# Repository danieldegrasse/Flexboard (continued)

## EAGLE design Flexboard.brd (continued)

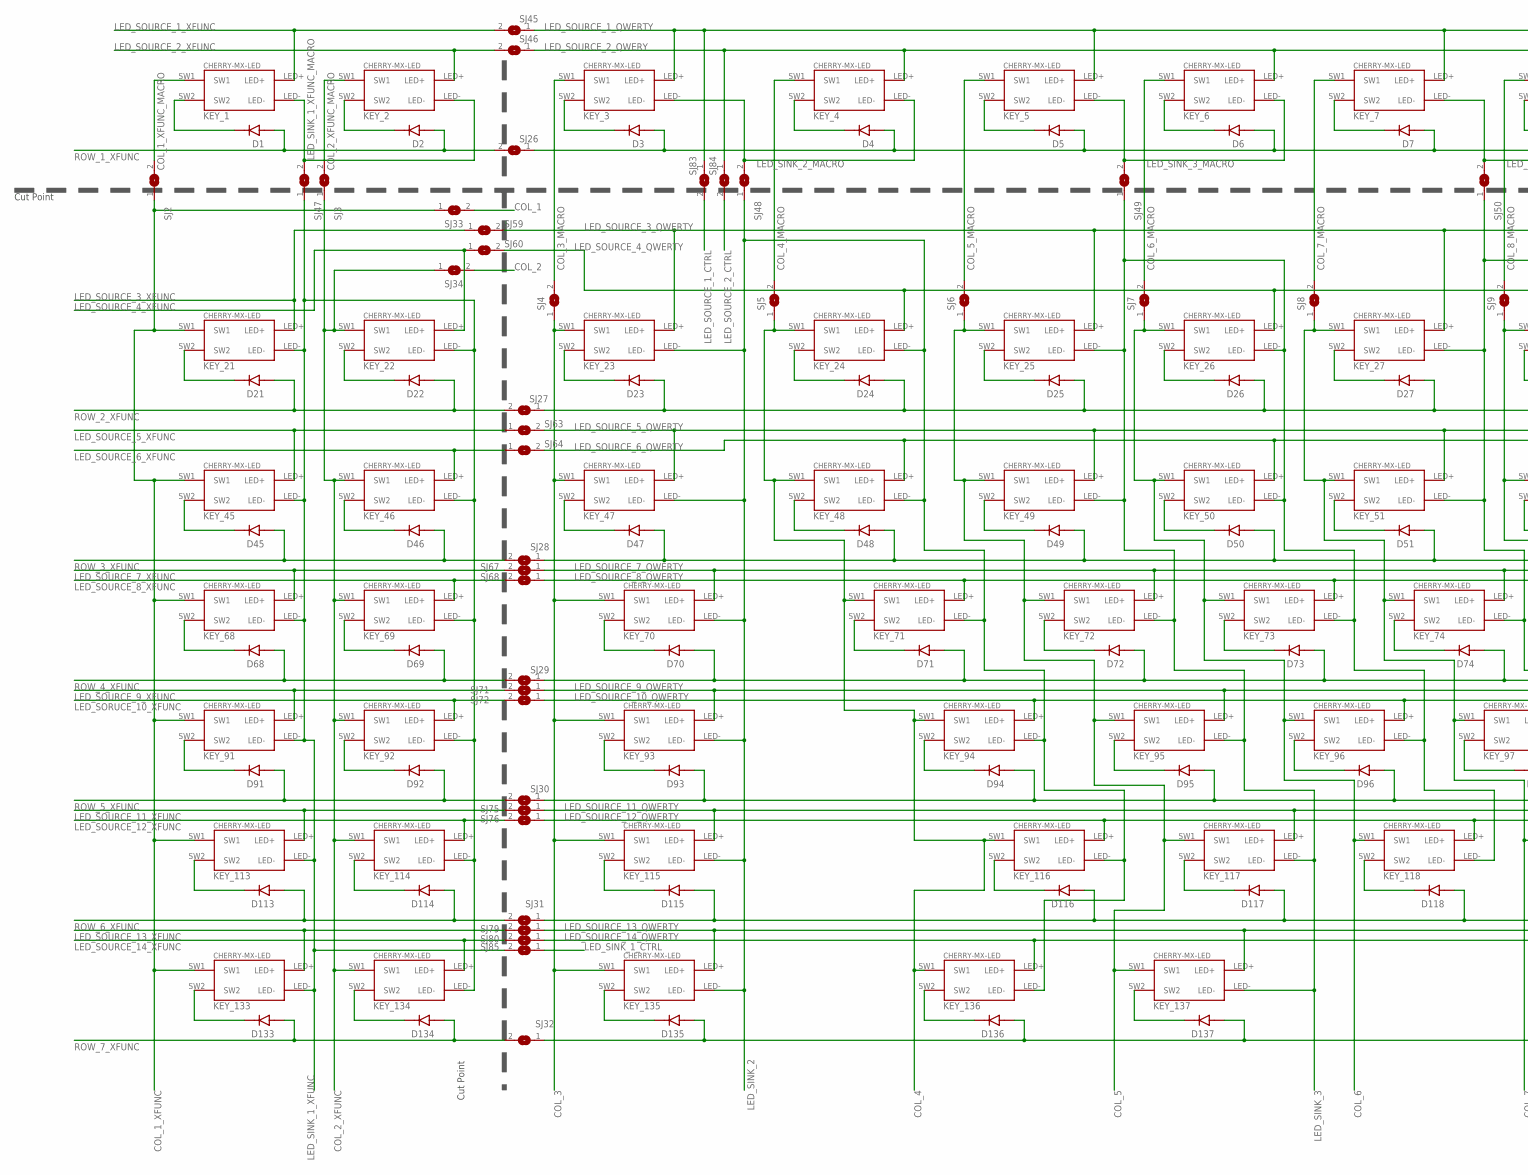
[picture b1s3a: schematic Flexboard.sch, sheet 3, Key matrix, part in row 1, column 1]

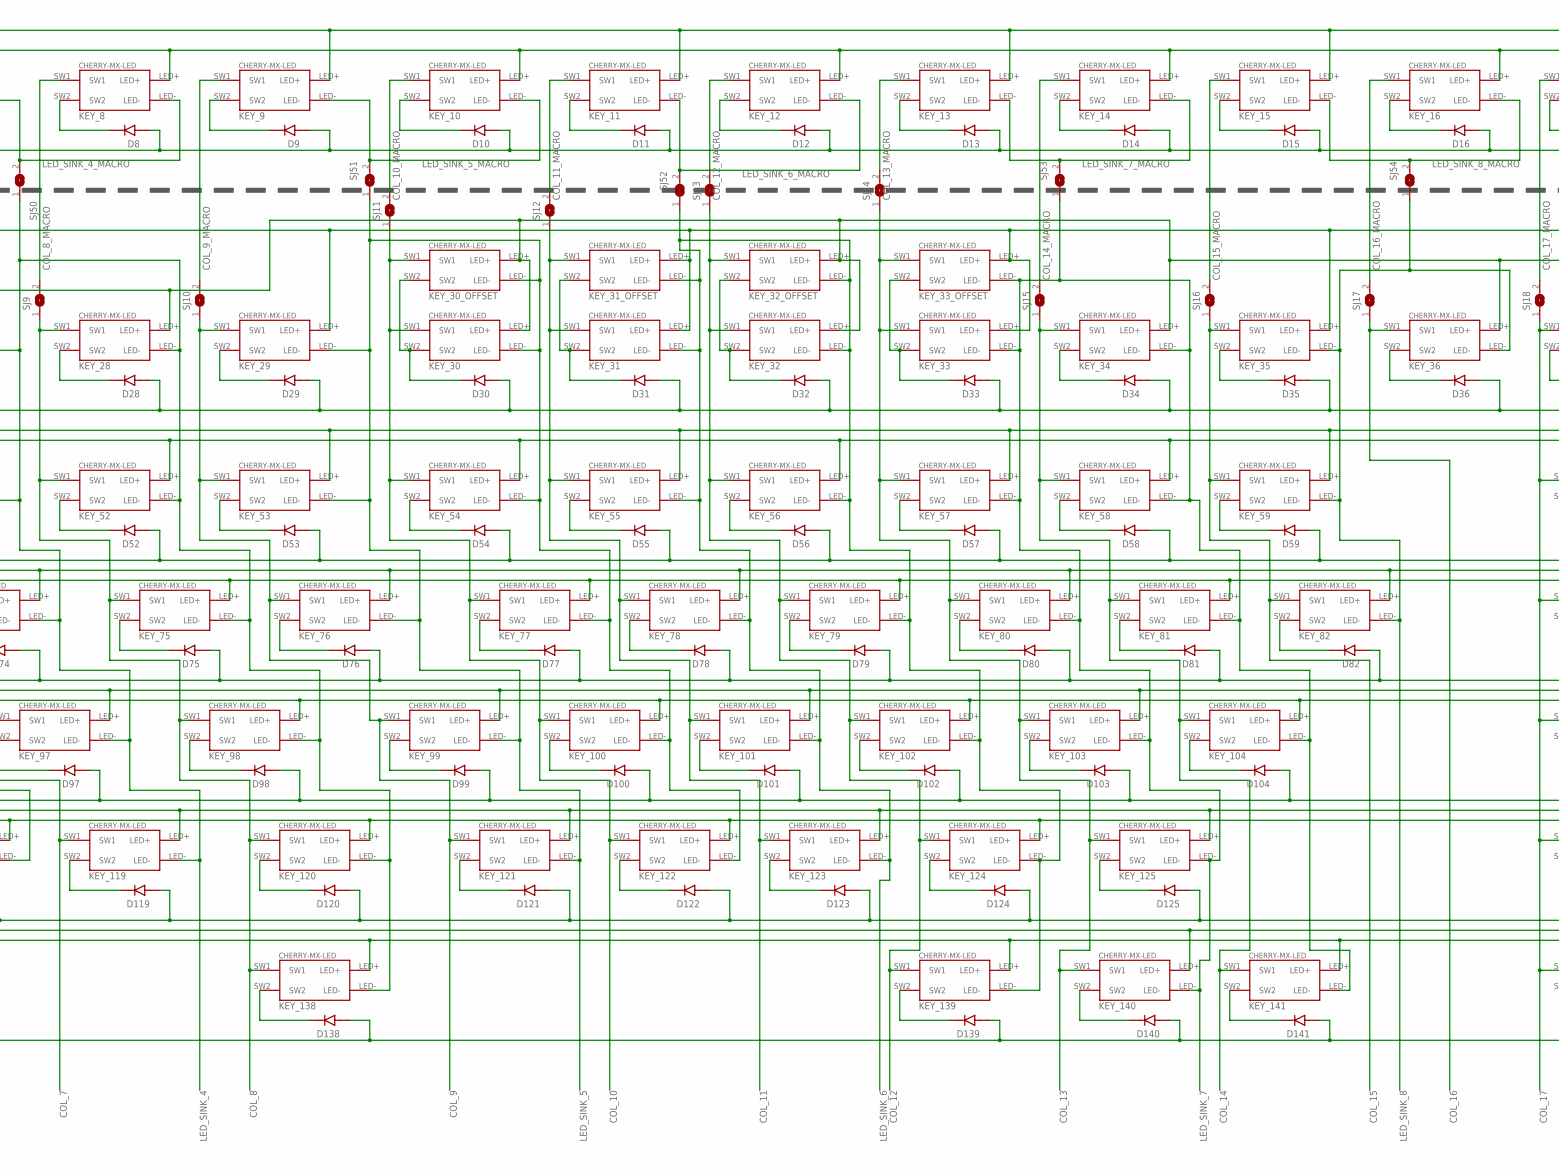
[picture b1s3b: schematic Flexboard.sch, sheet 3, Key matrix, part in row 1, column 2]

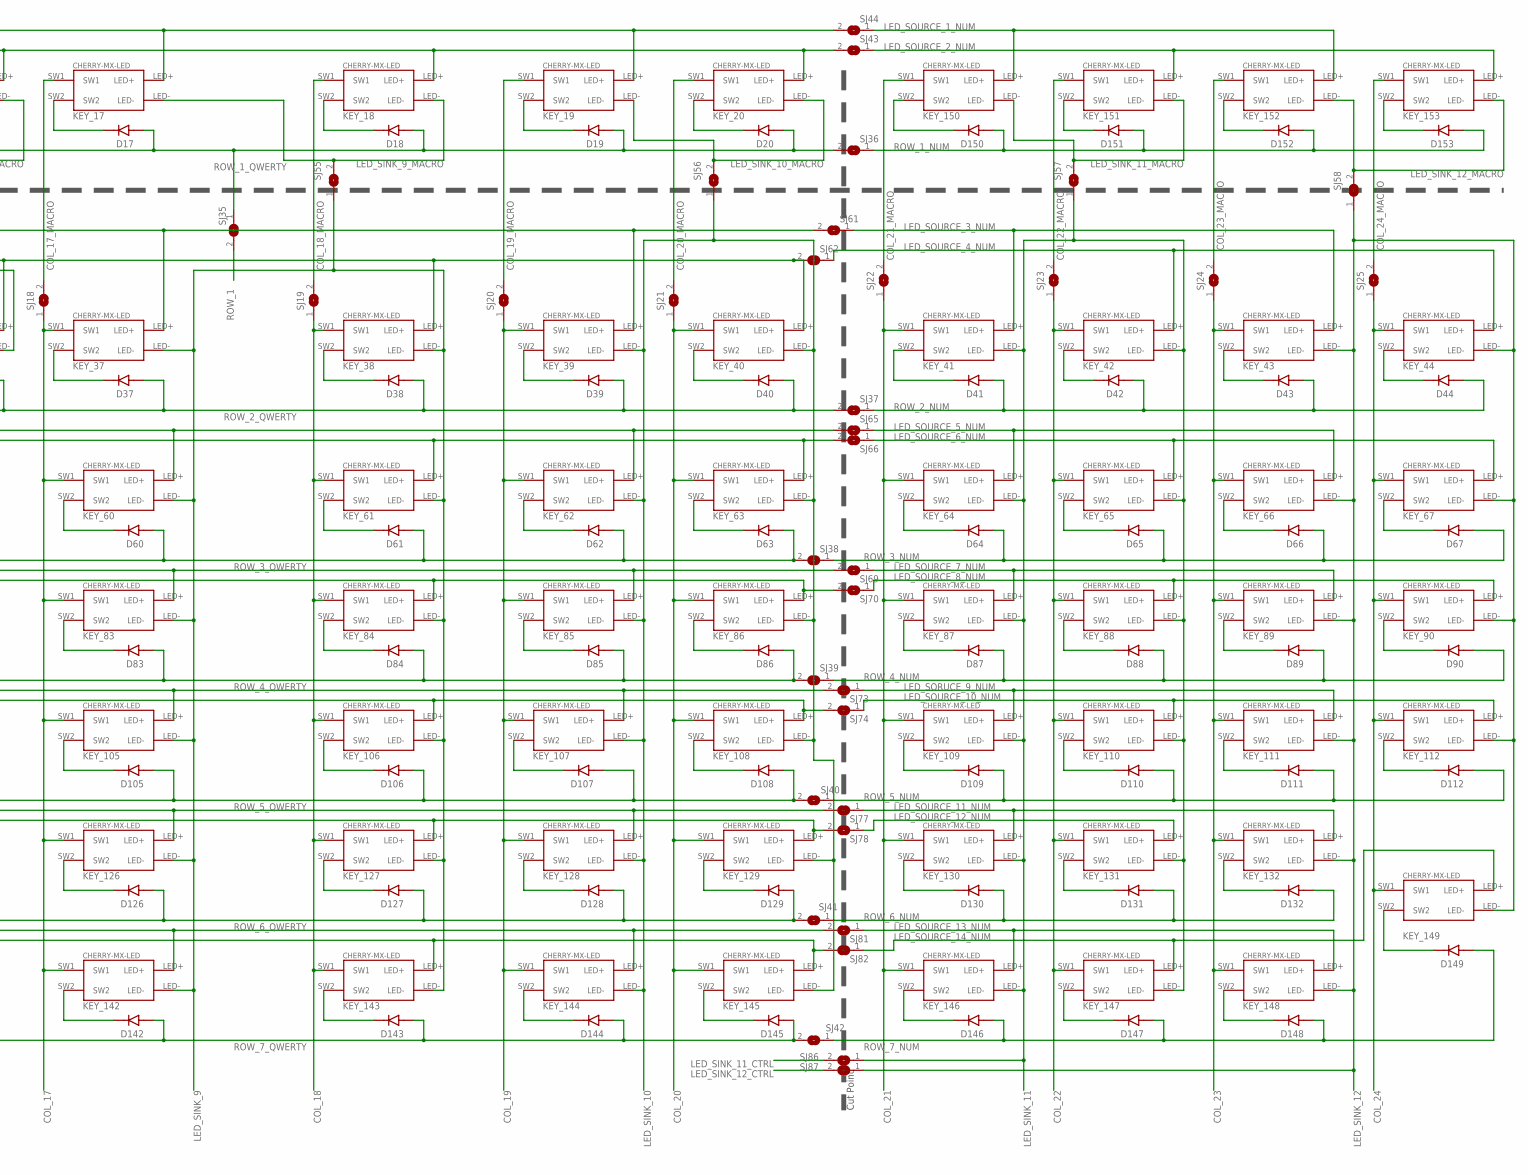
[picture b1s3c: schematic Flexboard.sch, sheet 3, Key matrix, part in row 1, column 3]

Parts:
D1, D2, D3, D4, D5, D6, D7, D8, D9, D10, D11, D12, D13, D14, D15, D16, D17, D18, D19, D20, D21, D22, D23, D24, D25, D26, D27, D28, D29, D30, D31, D32, D33, D34, D35, D36, D37, D38, D39, D40, D41, D42, D43, D44, D45, D46, D47, D48, D49, D50, D51, D52, D53, D54, D55, D56, D57, D58, D59, D60, D61, D62, D63, D64, D65, D66, D67, D68, D69, D70, D71, D72, D73, D74, D75, D76, D77, D78, D79, D80, D81, D82, D83, D84, D85, D86, D87, D88, D89, D90, D91, D92, D93, D94, D95, D96, D97, D98, D99, D100, D101, D102, D103, D104, D105, D106, D107, D108, D109, D110, D111, D112, D113, D114, D115, D116, D117, D118, D119, D120, D121, D122, D123, D124, D125, D126, D127, D128, D129, D130, D131, D132, D133, D134, D135, D136, D137, D138, D139, D140, D141, D142, D143, D144, D145, D146, D147, D148, D149, D150, D151, D152, D153: BAS16LT3G; SOT95P240X111-3N
KEY_1, KEY_2, KEY_3, KEY_4, KEY_5, KEY_6, KEY_7, KEY_8, KEY_9, KEY_10, KEY_11, KEY_12, KEY_13, KEY_14, KEY_15, KEY_16, KEY_17, KEY_18, KEY_19, KEY_20, KEY_21, KEY_22, KEY_23, KEY_24, KEY_25, KEY_26, KEY_27, KEY_28, KEY_29, KEY_30, KEY_31, KEY_32, KEY_33, KEY_34, KEY_35, KEY_36, KEY_37, KEY_38, KEY_39, KEY_40, KEY_41, KEY_42, KEY_43, KEY_44, KEY_45, KEY_46, KEY_47, KEY_48, KEY_49, KEY_50, KEY_51, KEY_52, KEY_53, KEY_54, KEY_55, KEY_56, KEY_57, KEY_58, KEY_59, KEY_60, KEY_61, KEY_62, KEY_63, KEY_64, KEY_65, KEY_66, KEY_67, KEY_68, KEY_69, KEY_70, KEY_71, KEY_72, KEY_73, KEY_74, KEY_75, KEY_76, KEY_77, KEY_78, KEY_79, KEY_80, KEY_81, KEY_82, KEY_83, KEY_84, KEY_85, KEY_86, KEY_87, KEY_88, KEY_89, KEY_90, KEY_91, KEY_92, KEY_93, KEY_94, KEY_95, KEY_96, KEY_97, KEY_98, KEY_99, KEY_100, KEY_101, KEY_102, KEY_103, KEY_104, KEY_105, KEY_106, KEY_107, KEY_108, KEY_109, KEY_110, KEY_111, KEY_112, KEY_113, KEY_114, KEY_115, KEY_116, KEY_117, KEY_118, KEY_119, KEY_120, KEY_121, KEY_122, KEY_123, KEY_124, KEY_125, KEY_126, KEY_127, KEY_128, KEY_129, KEY_130, KEY_131, KEY_132, KEY_133, KEY_134, KEY_135, KEY_136, KEY_137, KEY_138, KEY_139, KEY_140, KEY_141, KEY_142, KEY_143, KEY_144, KEY_145, KEY_146, KEY_147, KEY_148, KEY_149, KEY_150, KEY_151, KEY_152, KEY_153: CHERRY-MX-LED
KEY_30_OFFSET, KEY_31_OFFSET, KEY_32_OFFSET, KEY_33_OFFSET: CHERRY-MX-LED-NOPIN
SJ2, SJ3, SJ4, SJ5, SJ6, SJ7, SJ8, SJ9, SJ10, SJ11, SJ12, SJ13, SJ14, SJ15, SJ16, SJ17, SJ18, SJ19, SJ20, SJ21, SJ22, SJ23, SJ24, SJ25, SJ26, SJ27, SJ28, SJ29, SJ30, SJ31, SJ32, SJ33, SJ34, SJ35, SJ36, SJ37, SJ38, SJ39, SJ40, SJ41, SJ42, SJ43, SJ44, SJ45, SJ46, SJ47, SJ48, SJ49, SJ50, SJ51, SJ52, SJ53, SJ54, SJ55, SJ56, SJ57, SJ58, SJ59, SJ60, SJ61, SJ62, SJ63, SJ64, SJ65, SJ66, SJ67, SJ68, SJ69, SJ70, SJ71, SJ72, SJ73, SJ74, SJ75, SJ76, SJ77, SJ78, SJ79, SJ80, SJ81, SJ82, SJ83, SJ84, SJ85, SJ86, SJ87: SJW

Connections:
COL_1: SJ33.2; also elsewhere on the board
COL_1_XFUNC: KEY_21.SW1, KEY_45.SW1, KEY_68.SW1, KEY_91.SW1, KEY_113.SW1, KEY_133.SW1, SJ2.1, SJ33.1
COL_1_XFUNC_MACRO: KEY_1.SW1, SJ2.2
COL_2: SJ34.2; also elsewhere on the board
COL_2_XFUNC: KEY_22.SW1, KEY_46.SW1, KEY_69.SW1, KEY_92.SW1, KEY_114.SW1, KEY_134.SW1, SJ3.1, SJ34.1
COL_2_XFUNC_MACRO: KEY_2.SW1, SJ3.2
COL_3: KEY_23.SW1, KEY_47.SW1, KEY_70.SW1, KEY_93.SW1, KEY_115.SW1, KEY_135.SW1, SJ4.1; also elsewhere on the board
COL_3_MACRO: KEY_3.SW1, SJ4.2
COL_4: KEY_24.SW1, KEY_48.SW1, KEY_71.SW1, KEY_94.SW1, KEY_116.SW1, KEY_136.SW1, SJ5.1; also elsewhere on the board
COL_4_MACRO: KEY_4.SW1, SJ5.2
COL_5: KEY_25.SW1, KEY_49.SW1, KEY_72.SW1, KEY_95.SW1, KEY_117.SW1, KEY_137.SW1, SJ6.1; also elsewhere on the board
COL_5_MACRO: KEY_5.SW1, SJ6.2
COL_6: KEY_26.SW1, KEY_50.SW1, KEY_73.SW1, KEY_96.SW1, KEY_118.SW1, SJ7.1; also elsewhere on the board
COL_6_MACRO: KEY_6.SW1, SJ7.2
COL_7: KEY_27.SW1, KEY_51.SW1, KEY_74.SW1, KEY_97.SW1, KEY_119.SW1, SJ8.1; also elsewhere on the board
COL_7_MACRO: KEY_7.SW1, SJ8.2
COL_8: KEY_28.SW1, KEY_52.SW1, KEY_75.SW1, KEY_98.SW1, KEY_120.SW1, KEY_138.SW1, SJ9.1; also elsewhere on the board
COL_8_MACRO: KEY_8.SW1, SJ9.2
COL_9: KEY_29.SW1, KEY_53.SW1, KEY_76.SW1, KEY_99.SW1, KEY_121.SW1, SJ10.1; also elsewhere on the board
COL_9_MACRO: KEY_9.SW1, SJ10.2
COL_10: KEY_30.SW1, KEY_30_OFFSET.SW1, KEY_54.SW1, KEY_77.SW1, KEY_100.SW1, KEY_122.SW1, SJ11.1; also elsewhere on the board
COL_10_MACRO: KEY_10.SW1, SJ11.2
COL_11: KEY_31.SW1, KEY_31_OFFSET.SW1, KEY_55.SW1, KEY_78.SW1, KEY_101.SW1, KEY_123.SW1, SJ12.1; also elsewhere on the board
COL_11_MACRO: KEY_11.SW1, SJ12.2
COL_12: KEY_32.SW1, KEY_32_OFFSET.SW1, KEY_56.SW1, KEY_79.SW1, KEY_102.SW1, KEY_124.SW1, KEY_139.SW1, SJ13.1; also elsewhere on the board
COL_12_MACRO: KEY_12.SW1, SJ13.2
COL_13: KEY_33.SW1, KEY_33_OFFSET.SW1, KEY_57.SW1, KEY_80.SW1, KEY_103.SW1, KEY_125.SW1, KEY_140.SW1, SJ14.1; also elsewhere on the board
COL_13_MACRO: KEY_13.SW1, SJ14.2
COL_14: KEY_34.SW1, KEY_58.SW1, KEY_81.SW1, KEY_104.SW1, KEY_141.SW1, SJ15.1; also elsewhere on the board
COL_14_MACRO: KEY_14.SW1, SJ15.2
COL_15: KEY_35.SW1, KEY_59.SW1, KEY_82.SW1, SJ16.1; also elsewhere on the board
COL_15_MACRO: KEY_15.SW1, SJ16.2
COL_16: KEY_36.SW1, SJ17.1; also elsewhere on the board
COL_16_MACRO: KEY_16.SW1, SJ17.2
COL_17: KEY_37.SW1, KEY_60.SW1, KEY_83.SW1, KEY_105.SW1, KEY_126.SW1, KEY_142.SW1, SJ18.1; also elsewhere on the board
COL_17_MACRO: KEY_17.SW1, SJ18.2
COL_18: KEY_38.SW1, KEY_61.SW1, KEY_84.SW1, KEY_106.SW1, KEY_127.SW1, KEY_143.SW1, SJ19.1; also elsewhere on the board
COL_18_MACRO: KEY_18.SW1, SJ19.2
COL_19: KEY_39.SW1, KEY_62.SW1, KEY_85.SW1, KEY_107.SW1, KEY_128.SW1, KEY_144.SW1, SJ20.1; also elsewhere on the board
COL_19_MACRO: KEY_19.SW1, SJ20.2
COL_20: KEY_40.SW1, KEY_63.SW1, KEY_86.SW1, KEY_108.SW1, KEY_129.SW1, KEY_145.SW1, SJ21.1; also elsewhere on the board
COL_20_MACRO: KEY_20.SW1, SJ21.2
COL_21: KEY_41.SW1, KEY_64.SW1, KEY_87.SW1, KEY_109.SW1, KEY_130.SW1, KEY_146.SW1, SJ22.1; also elsewhere on the board
COL_21_MACRO: KEY_150.SW1, SJ22.2
COL_22: KEY_42.SW1, KEY_65.SW1, KEY_88.SW1, KEY_110.SW1, KEY_131.SW1, KEY_147.SW1, SJ23.1; also elsewhere on the board
COL_22_MACRO: KEY_151.SW1, SJ23.2
COL_23: KEY_43.SW1, KEY_66.SW1, KEY_89.SW1, KEY_111.SW1, KEY_132.SW1, KEY_148.SW1, SJ24.1; also elsewhere on the board
COL_23_MACRO: KEY_152.SW1, SJ24.2
COL_24: KEY_44.SW1, KEY_67.SW1, KEY_90.SW1, KEY_112.SW1, KEY_149.SW1, SJ25.1; also elsewhere on the board
COL_24_MACRO: KEY_153.SW1, SJ25.2
LED_SINK_1_CTRL: SJ85.1; also elsewhere on the board
LED_SINK_1_XFUNC: KEY_21.LED-, KEY_22.LED-, KEY_45.LED-, KEY_46.LED-, KEY_68.LED-, KEY_69.LED-, KEY_91.LED-, KEY_92.LED-, KEY_113.LED-, KEY_114.LED-, KEY_133.LED-, KEY_134.LED-, SJ47.1, SJ85.2
LED_SINK_1_XFUNC_MACRO: KEY_1.LED-, KEY_2.LED-, SJ47.2
LED_SINK_2: KEY_23.LED-, KEY_24.LED-, KEY_47.LED-, KEY_48.LED-, KEY_70.LED-, KEY_71.LED-, KEY_93.LED-, KEY_94.LED-, KEY_115.LED-, KEY_116.LED-, KEY_135.LED-, KEY_136.LED-, SJ48.1; also elsewhere on the board
LED_SINK_2_MACRO: KEY_3.LED-, KEY_4.LED-, SJ48.2
LED_SINK_3: KEY_25.LED-, KEY_26.LED-, KEY_49.LED-, KEY_50.LED-, KEY_72.LED-, KEY_73.LED-, KEY_95.LED-, KEY_96.LED-, KEY_117.LED-, KEY_118.LED-, KEY_137.LED-, SJ49.1; also elsewhere on the board
LED_SINK_3_MACRO: KEY_5.LED-, KEY_6.LED-, SJ49.2
LED_SINK_4: KEY_27.LED-, KEY_28.LED-, KEY_51.LED-, KEY_52.LED-, KEY_74.LED-, KEY_75.LED-, KEY_97.LED-, KEY_98.LED-, KEY_119.LED-, KEY_120.LED-, KEY_138.LED-, SJ50.1; also elsewhere on the board
LED_SINK_4_MACRO: KEY_7.LED-, KEY_8.LED-, SJ50.2
LED_SINK_5: KEY_29.LED-, KEY_30.LED-, KEY_30_OFFSET.LED-, KEY_53.LED-, KEY_54.LED-, KEY_76.LED-, KEY_77.LED-, KEY_99.LED-, KEY_100.LED-, KEY_121.LED-, KEY_122.LED-, SJ51.1; also elsewhere on the board
LED_SINK_5_MACRO: KEY_9.LED-, KEY_10.LED-, SJ51.2
LED_SINK_6: KEY_31.LED-, KEY_31_OFFSET.LED-, KEY_32.LED-, KEY_32_OFFSET.LED-, KEY_55.LED-, KEY_56.LED-, KEY_78.LED-, KEY_79.LED-, KEY_101.LED-, KEY_102.LED-, KEY_123.LED-, KEY_124.LED-, KEY_139.LED-, SJ52.1; also elsewhere on the board
LED_SINK_6_MACRO: KEY_11.LED-, KEY_12.LED-, SJ52.2
LED_SINK_7: KEY_33.LED-, KEY_33_OFFSET.LED-, KEY_34.LED-, KEY_57.LED-, KEY_58.LED-, KEY_80.LED-, KEY_81.LED-, KEY_103.LED-, KEY_104.LED-, KEY_125.LED-, KEY_140.LED-, KEY_141.LED-, SJ53.1; also elsewhere on the board
LED_SINK_7_MACRO: KEY_13.LED-, KEY_14.LED-, SJ53.2
LED_SINK_8: KEY_35.LED-, KEY_36.LED-, KEY_59.LED-, KEY_82.LED-, SJ54.1; also elsewhere on the board
LED_SINK_8_MACRO: KEY_15.LED-, KEY_16.LED-, SJ54.2
LED_SINK_9: KEY_37.LED-, KEY_38.LED-, KEY_60.LED-, KEY_61.LED-, KEY_83.LED-, KEY_84.LED-, KEY_105.LED-, KEY_106.LED-, KEY_126.LED-, KEY_127.LED-, KEY_142.LED-, KEY_143.LED-, SJ55.1; also elsewhere on the board
LED_SINK_9_MACRO: KEY_17.LED-, KEY_18.LED-, SJ55.2
LED_SINK_10: KEY_39.LED-, KEY_40.LED-, KEY_62.LED-, KEY_63.LED-, KEY_85.LED-, KEY_86.LED-, KEY_107.LED-, KEY_108.LED-, KEY_128.LED-, KEY_129.LED-, KEY_144.LED-, KEY_145.LED-, SJ56.1; also elsewhere on the board
LED_SINK_10_MACRO: KEY_19.LED-, KEY_20.LED-, SJ56.2
LED_SINK_11: KEY_41.LED-, KEY_42.LED-, KEY_64.LED-, KEY_65.LED-, KEY_87.LED-, KEY_88.LED-, KEY_109.LED-, KEY_110.LED-, KEY_130.LED-, KEY_131.LED-, KEY_146.LED-, KEY_147.LED-, SJ57.1, SJ86.1
LED_SINK_11_CTRL: SJ86.2; also elsewhere on the board
LED_SINK_11_MACRO: KEY_150.LED-, KEY_151.LED-, SJ57.2
LED_SINK_12: KEY_43.LED-, KEY_44.LED-, KEY_66.LED-, KEY_67.LED-, KEY_89.LED-, KEY_90.LED-, KEY_111.LED-, KEY_112.LED-, KEY_132.LED-, KEY_148.LED-, KEY_149.LED-, SJ58.1, SJ87.1
LED_SINK_12_CTRL: SJ87.2; also elsewhere on the board
LED_SINK_12_MACRO: KEY_152.LED-, KEY_153.LED-, SJ58.2
LED_SORUCE_9_NUM: KEY_109.LED+, KEY_111.LED+, SJ73.1
LED_SORUCE_10_XFUNC: KEY_92.LED+, SJ72.2
LED_SOURCE_1_CTRL: SJ83.2; also elsewhere on the board
LED_SOURCE_1_NUM: KEY_150.LED+, KEY_152.LED+, SJ44.1
LED_SOURCE_1_QWERTY: KEY_3.LED+, KEY_5.LED+, KEY_7.LED+, KEY_9.LED+, KEY_11.LED+, KEY_13.LED+, KEY_15.LED+, KEY_17.LED+, KEY_19.LED+, SJ44.2, SJ45.1, SJ83.1
LED_SOURCE_1_XFUNC: KEY_1.LED+, SJ45.2
LED_SOURCE_2_CTRL: SJ84.2; also elsewhere on the board
LED_SOURCE_2_NUM: KEY_151.LED+, KEY_153.LED+, SJ43.1
LED_SOURCE_2_QWERY: KEY_4.LED+, KEY_6.LED+, KEY_8.LED+, KEY_10.LED+, KEY_12.LED+, KEY_14.LED+, KEY_16.LED+, KEY_18.LED+, KEY_20.LED+, SJ43.2, SJ46.1, SJ84.1
LED_SOURCE_2_XFUNC: KEY_2.LED+, SJ46.2
LED_SOURCE_3_NUM: KEY_41.LED+, KEY_43.LED+, SJ61.1
LED_SOURCE_3_QWERTY: KEY_23.LED+, KEY_25.LED+, KEY_27.LED+, KEY_29.LED+, KEY_31.LED+, KEY_31_OFFSET.LED+, KEY_33.LED+, KEY_33_OFFSET.LED+, KEY_35.LED+, KEY_37.LED+, KEY_39.LED+, SJ59.2, SJ61.2; also elsewhere on the board
LED_SOURCE_3_XFUNC: KEY_21.LED+, SJ59.1
LED_SOURCE_4_NUM: KEY_42.LED+, KEY_44.LED+, SJ62.1
LED_SOURCE_4_QWERTY: KEY_24.LED+, KEY_26.LED+, KEY_28.LED+, KEY_30.LED+, KEY_30_OFFSET.LED+, KEY_32.LED+, KEY_32_OFFSET.LED+, KEY_34.LED+, KEY_36.LED+, KEY_38.LED+, KEY_40.LED+, SJ60.2, SJ62.2; also elsewhere on the board
LED_SOURCE_4_XFUNC: KEY_22.LED+, SJ60.1
LED_SOURCE_5_NUM: KEY_64.LED+, KEY_66.LED+, SJ65.1
LED_SOURCE_5_QWERTY: KEY_47.LED+, KEY_49.LED+, KEY_51.LED+, KEY_53.LED+, KEY_55.LED+, KEY_57.LED+, KEY_59.LED+, KEY_60.LED+, KEY_62.LED+, SJ63.2, SJ65.2; also elsewhere on the board
LED_SOURCE_5_XFUNC: KEY_45.LED+, SJ63.1
LED_SOURCE_6_NUM: KEY_65.LED+, KEY_67.LED+, SJ66.1
LED_SOURCE_6_QWERTY: KEY_48.LED+, KEY_50.LED+, KEY_52.LED+, KEY_54.LED+, KEY_56.LED+, KEY_58.LED+, KEY_61.LED+, KEY_63.LED+, SJ64.2, SJ66.2; also elsewhere on the board
LED_SOURCE_6_XFUNC: KEY_46.LED+, SJ64.1
LED_SOURCE_7_NUM: KEY_87.LED+, KEY_89.LED+, SJ69.1
LED_SOURCE_7_QWERTY: KEY_70.LED+, KEY_72.LED+, KEY_74.LED+, KEY_76.LED+, KEY_78.LED+, KEY_80.LED+, KEY_82.LED+, KEY_83.LED+, KEY_85.LED+, SJ67.1, SJ69.2; also elsewhere on the board
LED_SOURCE_7_XFUNC: KEY_68.LED+, SJ67.2
LED_SOURCE_8_NUM: KEY_88.LED+, KEY_90.LED+, SJ70.1
LED_SOURCE_8_QWERTY: KEY_71.LED+, KEY_73.LED+, KEY_75.LED+, KEY_77.LED+, KEY_79.LED+, KEY_81.LED+, KEY_84.LED+, KEY_86.LED+, SJ68.1, SJ70.2; also elsewhere on the board
LED_SOURCE_8_XFUNC: KEY_69.LED+, SJ68.2
LED_SOURCE_9_QWERTY: KEY_93.LED+, KEY_95.LED+, KEY_97.LED+, KEY_99.LED+, KEY_101.LED+, KEY_103.LED+, KEY_105.LED+, KEY_107.LED+, SJ71.1, SJ73.2; also elsewhere on the board
LED_SOURCE_9_XFUNC: KEY_91.LED+, SJ71.2
LED_SOURCE_10_NUM: KEY_110.LED+, KEY_112.LED+, SJ74.1
LED_SOURCE_10_QWERTY: KEY_94.LED+, KEY_96.LED+, KEY_98.LED+, KEY_100.LED+, KEY_102.LED+, KEY_104.LED+, KEY_106.LED+, KEY_108.LED+, SJ72.1, SJ74.2; also elsewhere on the board
LED_SOURCE_11_NUM: KEY_130.LED+, KEY_132.LED+, SJ77.1
LED_SOURCE_11_QWERTY: KEY_115.LED+, KEY_117.LED+, KEY_119.LED+, KEY_121.LED+, KEY_123.LED+, KEY_125.LED+, KEY_126.LED+, KEY_128.LED+, SJ75.1, SJ77.2; also elsewhere on the board
LED_SOURCE_11_XFUNC: KEY_113.LED+, SJ75.2
LED_SOURCE_12_NUM: KEY_131.LED+, SJ78.1
LED_SOURCE_12_QWERTY: KEY_116.LED+, KEY_118.LED+, KEY_120.LED+, KEY_122.LED+, KEY_124.LED+, KEY_127.LED+, KEY_129.LED+, SJ76.1, SJ78.2; also elsewhere on the board
LED_SOURCE_12_XFUNC: KEY_114.LED+, SJ76.2
LED_SOURCE_13_NUM: KEY_146.LED+, KEY_148.LED+, SJ81.1
LED_SOURCE_13_QWERTY: KEY_135.LED+, KEY_137.LED+, KEY_140.LED+, KEY_142.LED+, KEY_144.LED+, SJ79.1, SJ81.2; also elsewhere on the board
LED_SOURCE_13_XFUNC: KEY_133.LED+, SJ79.2
LED_SOURCE_14_NUM: KEY_147.LED+, KEY_149.LED+, SJ82.1
LED_SOURCE_14_QWERTY: KEY_136.LED+, KEY_138.LED+, KEY_139.LED+, KEY_141.LED+, KEY_143.LED+, KEY_145.LED+, SJ80.1, SJ82.2; also elsewhere on the board
LED_SOURCE_14_XFUNC: KEY_134.LED+, SJ80.2
unnamed: D1.3 (C), KEY_1.SW2
unnamed: D2.3 (C), KEY_2.SW2
unnamed: D3.3 (C), KEY_3.SW2
unnamed: D4.3 (C), KEY_4.SW2
unnamed: D5.3 (C), KEY_5.SW2
unnamed: D6.3 (C), KEY_6.SW2
unnamed: D7.3 (C), KEY_7.SW2
unnamed: D8.3 (C), KEY_8.SW2
unnamed: D9.3 (C), KEY_9.SW2
unnamed: D10.3 (C), KEY_10.SW2
unnamed: D31.3 (C), KEY_31.SW2, KEY_31_OFFSET.SW2
unnamed: D11.3 (C), KEY_11.SW2
unnamed: D40.3 (C), KEY_40.SW2
unnamed: D12.3 (C), KEY_12.SW2
unnamed: D39.3 (C), KEY_39.SW2
unnamed: D13.3 (C), KEY_13.SW2
unnamed: D25.3 (C), KEY_25.SW2
unnamed: D14.3 (C), KEY_14.SW2
unnamed: D38.3 (C), KEY_38.SW2
unnamed: D15.3 (C), KEY_15.SW2
unnamed: D35.3 (C), KEY_35.SW2
unnamed: D16.3 (C), KEY_16.SW2
unnamed: D34.3 (C), KEY_34.SW2
unnamed: D17.3 (C), KEY_17.SW2
unnamed: D37.3 (C), KEY_37.SW2
unnamed: D18.3 (C), KEY_18.SW2
unnamed: D30.3 (C), KEY_30.SW2, KEY_30_OFFSET.SW2
unnamed: D19.3 (C), KEY_19.SW2
unnamed: D36.3 (C), KEY_36.SW2
unnamed: D20.3 (C), KEY_20.SW2
unnamed: D33.3 (C), KEY_33.SW2, KEY_33_OFFSET.SW2
unnamed: D23.3 (C), KEY_23.SW2
unnamed: D32.3 (C), KEY_32.SW2, KEY_32_OFFSET.SW2
unnamed: D29.3 (C), KEY_29.SW2
unnamed: D24.3 (C), KEY_24.SW2
unnamed: D28.3 (C), KEY_28.SW2
unnamed: D27.3 (C), KEY_27.SW2
unnamed: D22.3 (C), KEY_22.SW2
unnamed: D26.3 (C), KEY_26.SW2
unnamed: D21.3 (C), KEY_21.SW2
unnamed: D45.3 (C), KEY_45.SW2
unnamed: D41.3 (C), KEY_41.SW2
unnamed: D46.3 (C), KEY_46.SW2
unnamed: D67.3 (C), KEY_67.SW2
unnamed: D66.3 (C), KEY_66.SW2
unnamed: D68.3 (C), KEY_68.SW2
unnamed: D65.3 (C), KEY_65.SW2
unnamed: D64.3 (C), KEY_64.SW2
unnamed: D63.3 (C), KEY_63.SW2
unnamed: D62.3 (C), KEY_62.SW2
unnamed: D61.3 (C), KEY_61.SW2
unnamed: D52.3 (C), KEY_52.SW2
unnamed: D49.3 (C), KEY_49.SW2
unnamed: D60.3 (C), KEY_60.SW2
unnamed: D51.3 (C), KEY_51.SW2
unnamed: D59.3 (C), KEY_59.SW2
unnamed: D58.3 (C), KEY_58.SW2
unnamed: D57.3 (C), KEY_57.SW2
unnamed: D50.3 (C), KEY_50.SW2
unnamed: D48.3 (C), KEY_48.SW2
unnamed: D56.3 (C), KEY_56.SW2
unnamed: D69.3 (C), KEY_69.SW2
unnamed: D55.3 (C), KEY_55.SW2
unnamed: D47.3 (C), KEY_47.SW2
unnamed: D54.3 (C), KEY_54.SW2
unnamed: D90.3 (C), KEY_90.SW2
unnamed: D53.3 (C), KEY_53.SW2
unnamed: D150.3 (C), KEY_150.SW2
unnamed: D89.3 (C), KEY_89.SW2
unnamed: D87.3 (C), KEY_87.SW2
unnamed: D70.3 (C), KEY_70.SW2
unnamed: D88.3 (C), KEY_88.SW2
unnamed: D83.3 (C), KEY_83.SW2
unnamed: D86.3 (C), KEY_86.SW2
unnamed: D71.3 (C), KEY_71.SW2
unnamed: D151.3 (C), KEY_151.SW2
unnamed: D72.3 (C), KEY_72.SW2
unnamed: D84.3 (C), KEY_84.SW2
unnamed: D73.3 (C), KEY_73.SW2
unnamed: D74.3 (C), KEY_74.SW2
unnamed: D85.3 (C), KEY_85.SW2
unnamed: D75.3 (C), KEY_75.SW2
unnamed: D112.3 (C), KEY_112.SW2
unnamed: D76.3 (C), KEY_76.SW2
unnamed: D111.3 (C), KEY_111.SW2
unnamed: D77.3 (C), KEY_77.SW2
unnamed: D110.3 (C), KEY_110.SW2
unnamed: D78.3 (C), KEY_78.SW2
unnamed: D96.3 (C), KEY_96.SW2
unnamed: D79.3 (C), KEY_79.SW2
unnamed: D109.3 (C), KEY_109.SW2
unnamed: D80.3 (C), KEY_80.SW2
unnamed: D113.3 (C), KEY_113.SW2
unnamed: D81.3 (C), KEY_81.SW2
unnamed: D108.3 (C), KEY_108.SW2
unnamed: D82.3 (C), KEY_82.SW2
unnamed: D100.3 (C), KEY_100.SW2
unnamed: D107.3 (C), KEY_107.SW2
unnamed: D106.3 (C), KEY_106.SW2
unnamed: D152.3 (C), KEY_152.SW2
unnamed: D99.3 (C), KEY_99.SW2
unnamed: D105.3 (C), KEY_105.SW2
unnamed: D104.3 (C), KEY_104.SW2
unnamed: D95.3 (C), KEY_95.SW2
unnamed: D103.3 (C), KEY_103.SW2
unnamed: D98.3 (C), KEY_98.SW2
unnamed: D97.3 (C), KEY_97.SW2
unnamed: D102.3 (C), KEY_102.SW2
unnamed: D101.3 (C), KEY_101.SW2
unnamed: D114.3 (C), KEY_114.SW2
unnamed: D94.3 (C), KEY_94.SW2
unnamed: D132.3 (C), KEY_132.SW2
unnamed: D93.3 (C), KEY_93.SW2
unnamed: D153.3 (C), KEY_153.SW2
unnamed: D92.3 (C), KEY_92.SW2
unnamed: D91.3 (C), KEY_91.SW2
unnamed: D131.3 (C), KEY_131.SW2
unnamed: D129.3 (C), KEY_129.SW2
unnamed: D130.3 (C), KEY_130.SW2
unnamed: D128.3 (C), KEY_128.SW2
unnamed: D124.3 (C), KEY_124.SW2
unnamed: D127.3 (C), KEY_127.SW2
unnamed: D125.3 (C), KEY_125.SW2
unnamed: D126.3 (C), KEY_126.SW2
unnamed: D133.3 (C), KEY_133.SW2
unnamed: D123.3 (C), KEY_123.SW2
unnamed: D122.3 (C), KEY_122.SW2
unnamed: D134.3 (C), KEY_134.SW2
unnamed: D121.3 (C), KEY_121.SW2
unnamed: D149.3 (C), KEY_149.SW2
unnamed: D120.3 (C), KEY_120.SW2
unnamed: D42.3 (C), KEY_42.SW2
unnamed: D119.3 (C), KEY_119.SW2
unnamed: D146.3 (C), KEY_146.SW2
unnamed: D118.3 (C), KEY_118.SW2
unnamed: D148.3 (C), KEY_148.SW2
unnamed: D117.3 (C), KEY_117.SW2
unnamed: D144.3 (C), KEY_144.SW2
unnamed: D116.3 (C), KEY_116.SW2
unnamed: D147.3 (C), KEY_147.SW2
unnamed: D145.3 (C), KEY_145.SW2
unnamed: D115.3 (C), KEY_115.SW2
unnamed: D143.3 (C), KEY_143.SW2
unnamed: D135.3 (C), KEY_135.SW2
unnamed: D142.3 (C), KEY_142.SW2
unnamed: D141.3 (C), KEY_141.SW2
unnamed: D140.3 (C), KEY_140.SW2
unnamed: D139.3 (C), KEY_139.SW2
unnamed: D43.3 (C), KEY_43.SW2
unnamed: D138.3 (C), KEY_138.SW2
unnamed: D137.3 (C), KEY_137.SW2
unnamed: D136.3 (C), KEY_136.SW2
unnamed: D44.3 (C), KEY_44.SW2
ROW_1: SJ35.2; also elsewhere on the board
ROW_1_NUM: D150.1 (A), D151.1 (A), D152.1 (A), D153.1 (A), SJ36.1
ROW_1_QWERTY: D3.1 (A), D4.1 (A), D5.1 (A), D6.1 (A), D7.1 (A), D8.1 (A), D9.1 (A), D10.1 (A), D11.1 (A), D12.1 (A), D13.1 (A), D14.1 (A), D15.1 (A), D16.1 (A), D17.1 (A), D18.1 (A), D19.1 (A), D20.1 (A), SJ26.1, SJ35.1, SJ36.2
ROW_1_XFUNC: D1.1 (A), D2.1 (A), SJ26.2
ROW_2_NUM: D41.1 (A), D42.1 (A), D43.1 (A), D44.1 (A), SJ37.1
ROW_2_QWERTY: D23.1 (A), D24.1 (A), D25.1 (A), D26.1 (A), D27.1 (A), D28.1 (A), D29.1 (A), D30.1 (A), D31.1 (A), D32.1 (A), D33.1 (A), D34.1 (A), D35.1 (A), D36.1 (A), D37.1 (A), D38.1 (A), D39.1 (A), D40.1 (A), SJ27.1, SJ37.2; also elsewhere on the board
ROW_2_XFUNC: D21.1 (A), D22.1 (A), SJ27.2
ROW_3_NUM: D64.1 (A), D65.1 (A), D66.1 (A), D67.1 (A), SJ38.1
ROW_3_QWERTY: D47.1 (A), D48.1 (A), D49.1 (A), D50.1 (A), D51.1 (A), D52.1 (A), D53.1 (A), D54.1 (A), D55.1 (A), D56.1 (A), D57.1 (A), D58.1 (A), D59.1 (A), D60.1 (A), D61.1 (A), D62.1 (A), D63.1 (A), SJ28.1, SJ38.2; also elsewhere on the board
ROW_3_XFUNC: D45.1 (A), D46.1 (A), SJ28.2
ROW_4_NUM: D87.1 (A), D88.1 (A), D89.1 (A), D90.1 (A), SJ39.1
ROW_4_QWERTY: D70.1 (A), D71.1 (A), D72.1 (A), D73.1 (A), D74.1 (A), D75.1 (A), D76.1 (A), D77.1 (A), D78.1 (A), D79.1 (A), D80.1 (A), D81.1 (A), D82.1 (A), D83.1 (A), D84.1 (A), D85.1 (A), D86.1 (A), SJ29.1, SJ39.2; also elsewhere on the board
ROW_4_XFUNC: D68.1 (A), D69.1 (A), SJ29.2
ROW_5_NUM: D109.1 (A), D110.1 (A), D111.1 (A), D112.1 (A), SJ40.1
ROW_5_QWERTY: D93.1 (A), D94.1 (A), D95.1 (A), D96.1 (A), D97.1 (A), D98.1 (A), D99.1 (A), D100.1 (A), D101.1 (A), D102.1 (A), D103.1 (A), D104.1 (A), D105.1 (A), D106.1 (A), D107.1 (A), D108.1 (A), SJ30.1, SJ40.2; also elsewhere on the board
ROW_5_XFUNC: D91.1 (A), D92.1 (A), SJ30.2
ROW_6_NUM: D130.1 (A), D131.1 (A), D132.1 (A), SJ41.1
ROW_6_QWERTY: D115.1 (A), D116.1 (A), D117.1 (A), D118.1 (A), D119.1 (A), D120.1 (A), D121.1 (A), D122.1 (A), D123.1 (A), D124.1 (A), D125.1 (A), D126.1 (A), D127.1 (A), D128.1 (A), D129.1 (A), SJ31.1, SJ41.2; also elsewhere on the board
ROW_6_XFUNC: D113.1 (A), D114.1 (A), SJ31.2
ROW_7_NUM: D146.1 (A), D147.1 (A), D148.1 (A), D149.1 (A), SJ42.1
ROW_7_QWERTY: D135.1 (A), D136.1 (A), D137.1 (A), D138.1 (A), D139.1 (A), D140.1 (A), D141.1 (A), D142.1 (A), D143.1 (A), D144.1 (A), D145.1 (A), SJ32.1, SJ42.2; also elsewhere on the board
ROW_7_XFUNC: D133.1 (A), D134.1 (A), SJ32.2

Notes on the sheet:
Cut Point

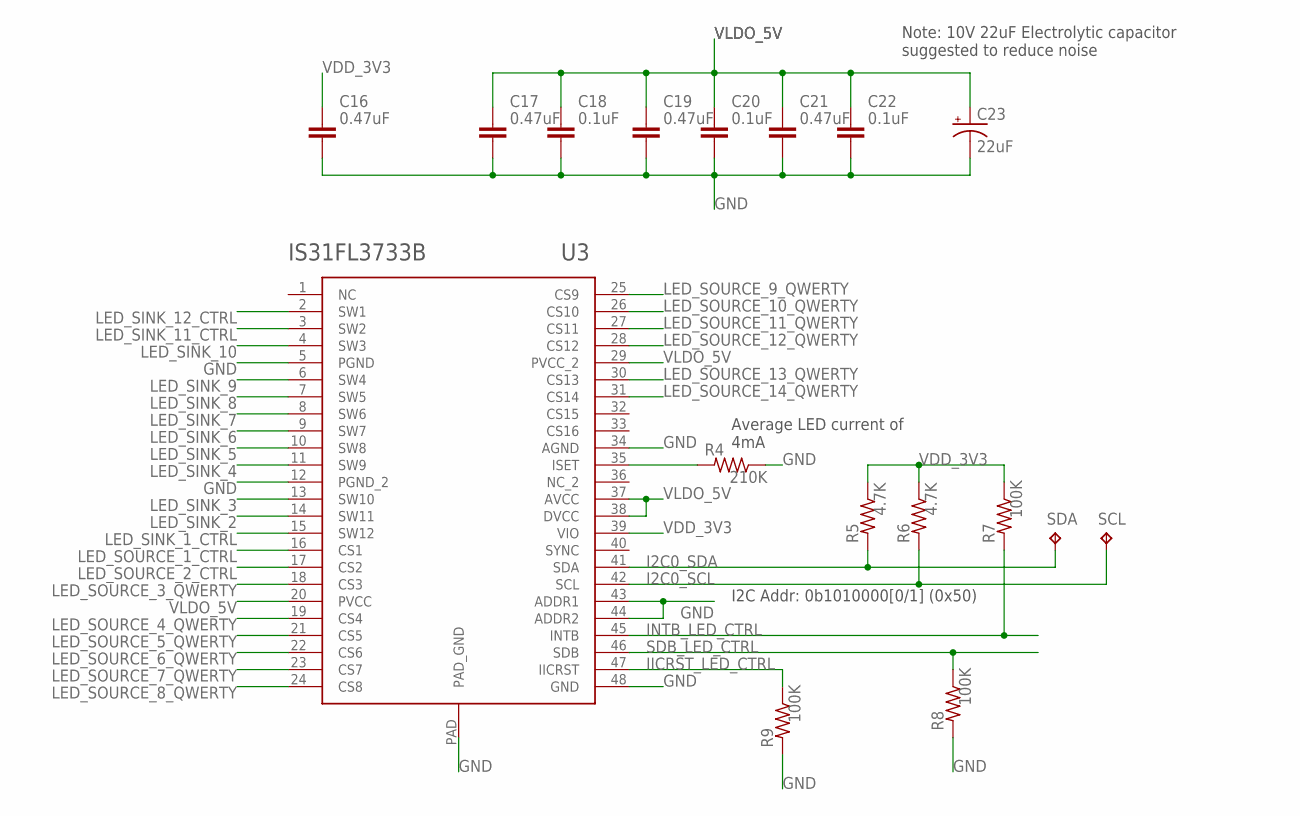
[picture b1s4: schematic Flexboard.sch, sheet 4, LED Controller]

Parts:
C16, C17, C19, C21: 0.47uF; CAPC2012X110
C18, C20, C22: 0.1uF; CAPC2012X110
C23: 22uF; 860020672011
R4: 210K; RESC2012X65
R5, R6: 4.7K; RESC2012X65
R7, R8, R9: 100K; RESC2012X65
SCL: TPB2,54; B2,54
SDA: TPB2,54; B2,54
U3: IS31FL3733B-TQLS4

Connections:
GND: C16.2, C17.2, C18.2, C19.2, C20.2, C21.2, C22.2, C23.-, R4.1, R8.2, R9.2, U3.5 (PGND), U3.12 (PGND_2), U3.34 (AGND), U3.43 (ADDR1), U3.44 (ADDR2), U3.48 (GND), U3.PAD (PAD_GND); also elsewhere on the board
I2C0_SCL: R6.2, SCL.TP, U3.42 (SCL); also elsewhere on the board
I2C0_SDA: R5.2, SDA.TP, U3.41 (SDA); also elsewhere on the board
IICRST_LED_CTRL: R9.1, U3.47 (IICRST)
INTB_LED_CTRL: R7.2, U3.45 (INTB); also elsewhere on the board
LED_SINK_1_CTRL: U3.15 (SW12); also elsewhere on the board
LED_SINK_2: U3.14 (SW11); also elsewhere on the board
LED_SINK_3: U3.13 (SW10); also elsewhere on the board
LED_SINK_4: U3.11 (SW9); also elsewhere on the board
LED_SINK_5: U3.10 (SW8); also elsewhere on the board
LED_SINK_6: U3.9 (SW7); also elsewhere on the board
LED_SINK_7: U3.8 (SW6); also elsewhere on the board
LED_SINK_8: U3.7 (SW5); also elsewhere on the board
LED_SINK_9: U3.6 (SW4); also elsewhere on the board
LED_SINK_10: U3.4 (SW3); also elsewhere on the board
LED_SINK_11_CTRL: U3.3 (SW2); also elsewhere on the board
LED_SINK_12_CTRL: U3.2 (SW1); also elsewhere on the board
LED_SOURCE_1_CTRL: U3.16 (CS1); also elsewhere on the board
LED_SOURCE_2_CTRL: U3.17 (CS2); also elsewhere on the board
LED_SOURCE_3_QWERTY: U3.18 (CS3); also elsewhere on the board
LED_SOURCE_4_QWERTY: U3.19 (CS4); also elsewhere on the board
LED_SOURCE_5_QWERTY: U3.21 (CS5); also elsewhere on the board
LED_SOURCE_6_QWERTY: U3.22 (CS6); also elsewhere on the board
LED_SOURCE_7_QWERTY: U3.23 (CS7); also elsewhere on the board
LED_SOURCE_8_QWERTY: U3.24 (CS8); also elsewhere on the board
LED_SOURCE_9_QWERTY: U3.25 (CS9); also elsewhere on the board
LED_SOURCE_10_QWERTY: U3.26 (CS10); also elsewhere on the board
LED_SOURCE_11_QWERTY: U3.27 (CS11); also elsewhere on the board
LED_SOURCE_12_QWERTY: U3.28 (CS12); also elsewhere on the board
LED_SOURCE_13_QWERTY: U3.30 (CS13); also elsewhere on the board
LED_SOURCE_14_QWERTY: U3.31 (CS14); also elsewhere on the board
unnamed: R4.2, U3.35 (ISET)
SDB_LED_CTRL: R8.1, U3.46 (SDB); also elsewhere on the board
VDD_3V3: C16.1, R5.1, R6.1, R7.1, U3.39 (VIO); also elsewhere on the board
VLDO_5V: C17.1, C18.1, C19.1, C20.1, C21.1, C22.1, C23.+, U3.20 (PVCC), U3.29 (PVCC_2), U3.37 (AVCC), U3.38 (DVCC); also elsewhere on the board

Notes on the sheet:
Average LED current of 4mA
I2C Addr: 0b1010000[0/1] (0x50)
Note: 10V 22uF Electrolytic capacitor suggested to reduce noise
